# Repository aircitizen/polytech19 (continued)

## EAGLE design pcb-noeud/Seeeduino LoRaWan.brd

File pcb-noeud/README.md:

# PCB noeud

Ici se situent les fichiers EAGLE du PCB du noeud.
Il y a également la BOM et des images.

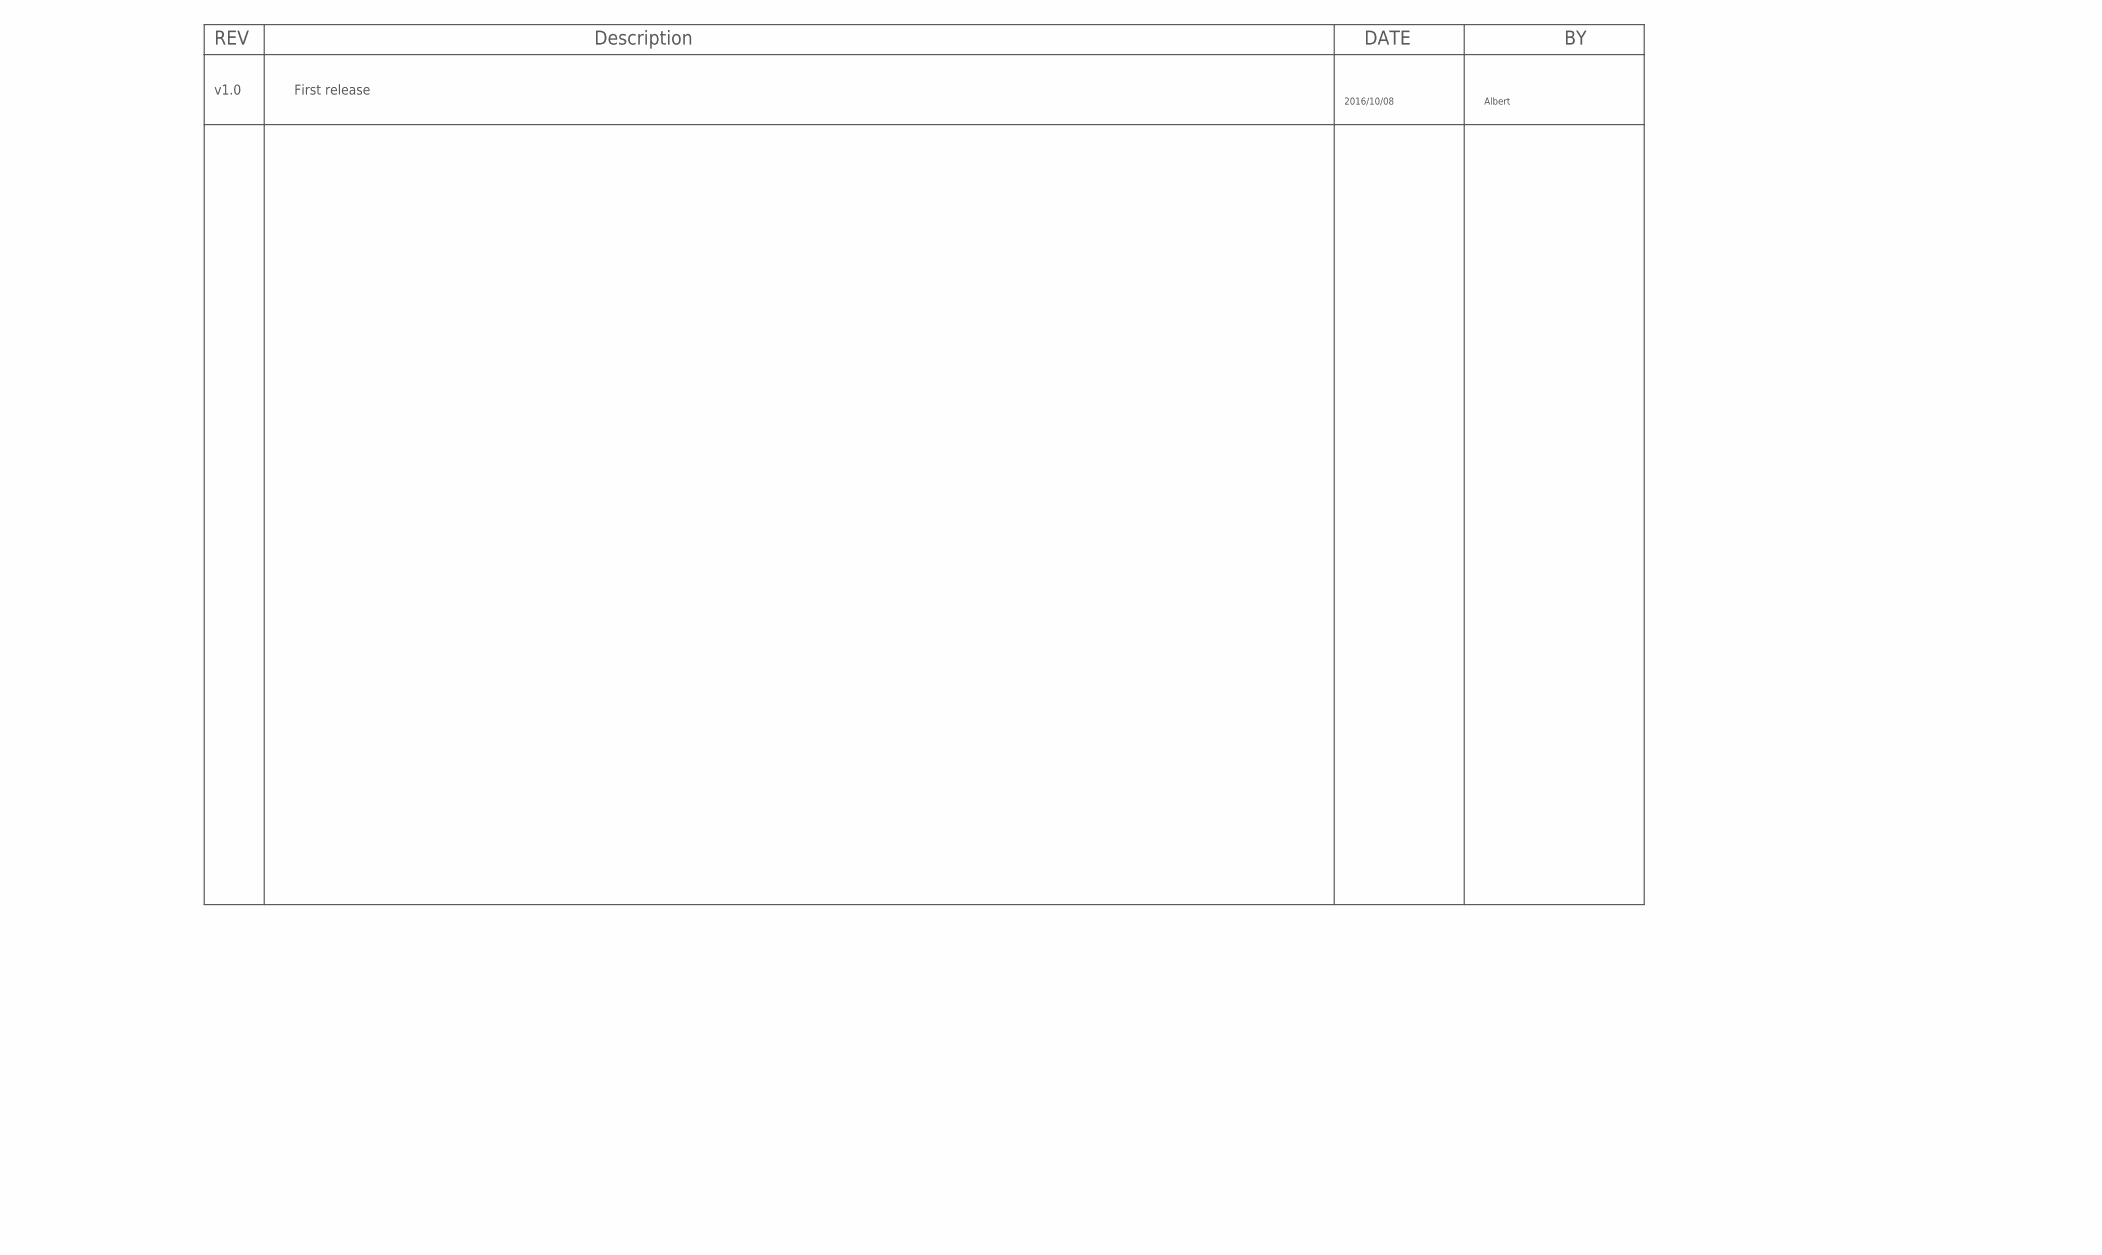
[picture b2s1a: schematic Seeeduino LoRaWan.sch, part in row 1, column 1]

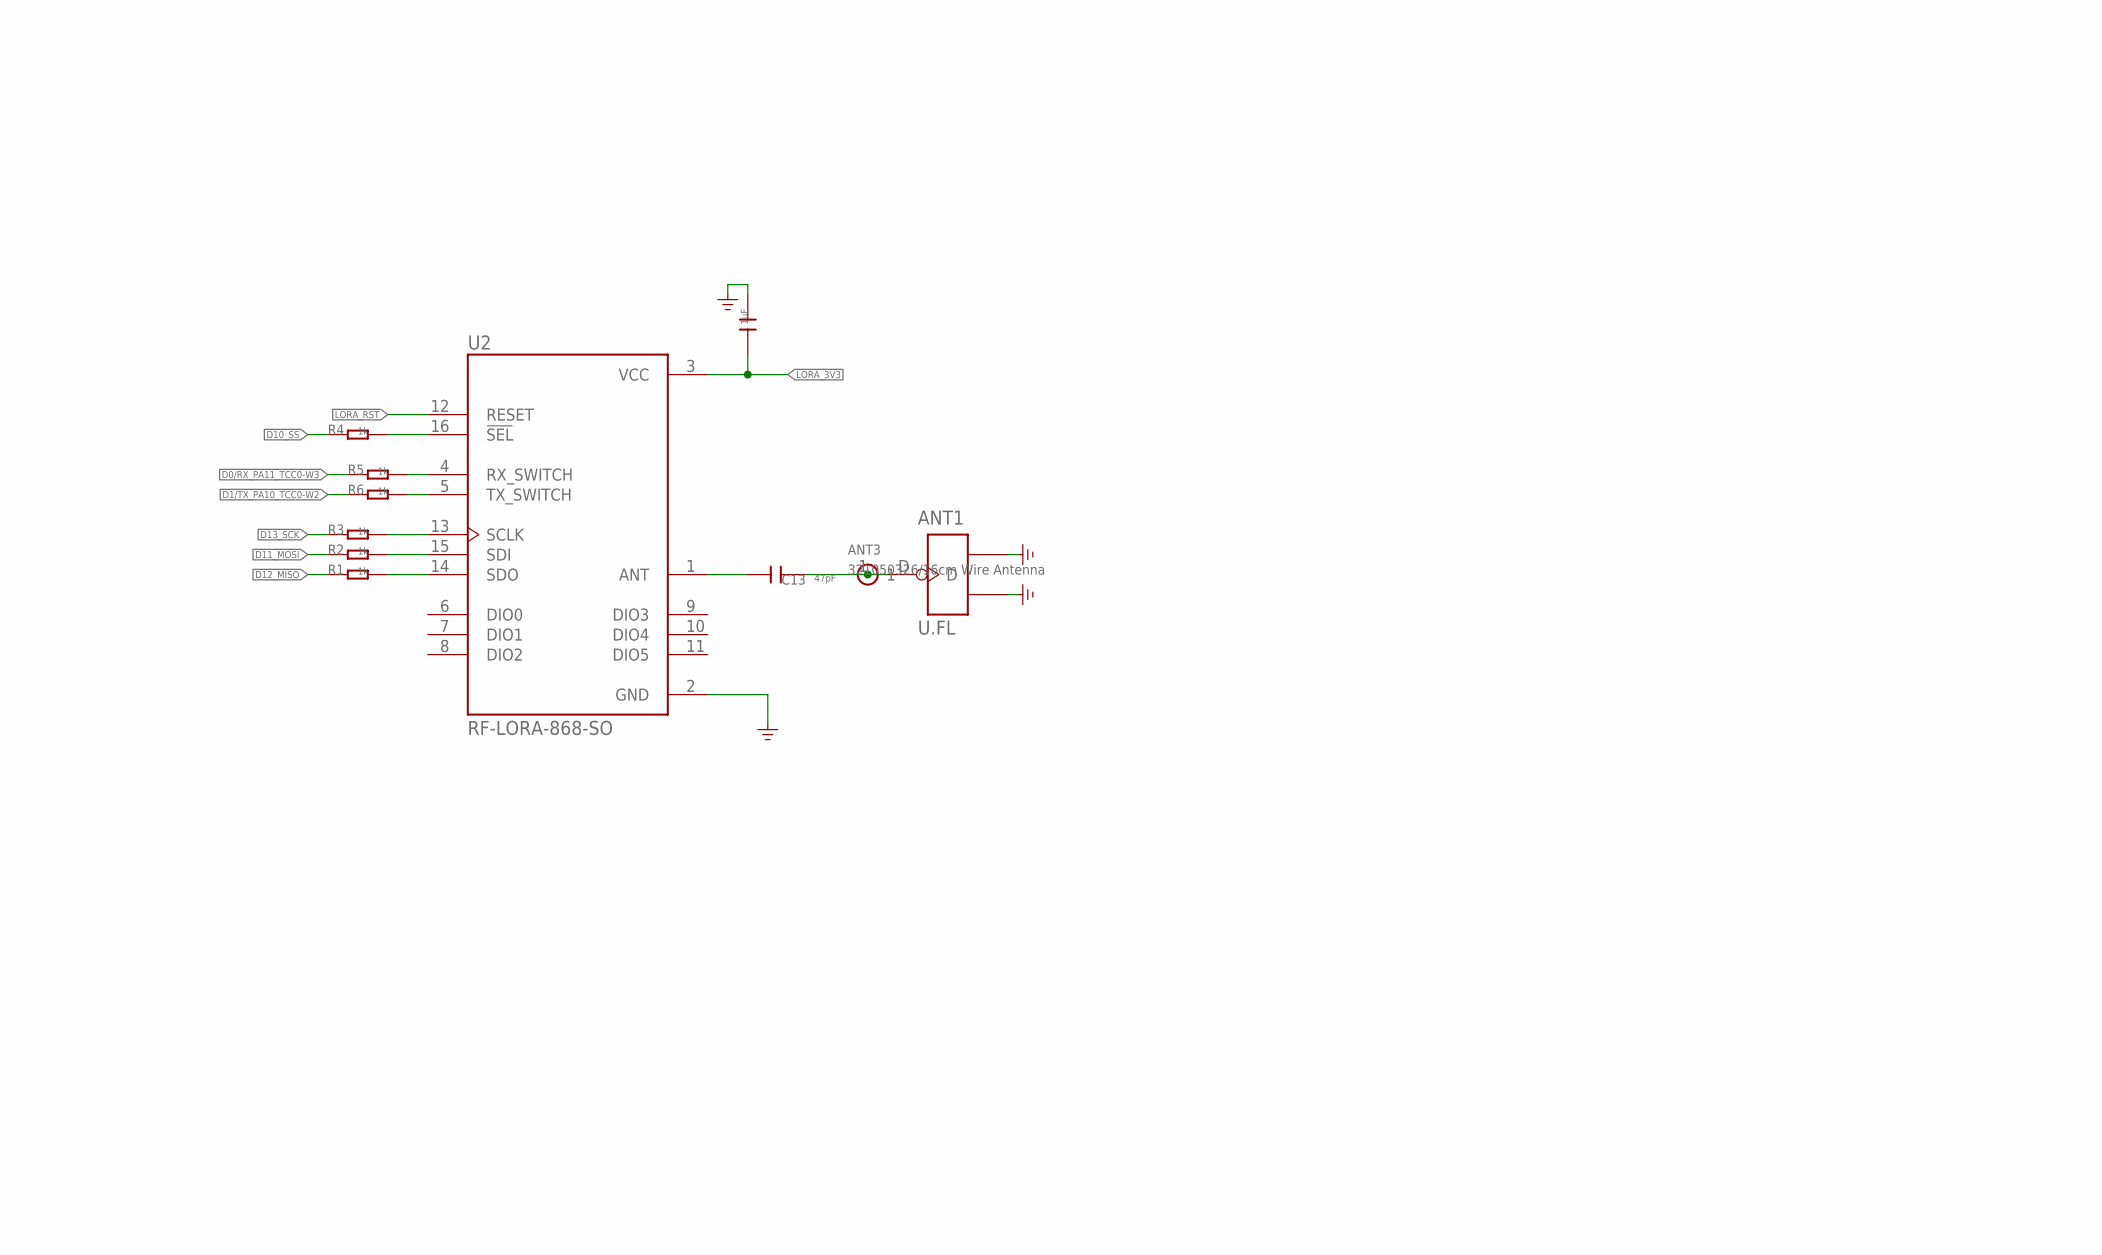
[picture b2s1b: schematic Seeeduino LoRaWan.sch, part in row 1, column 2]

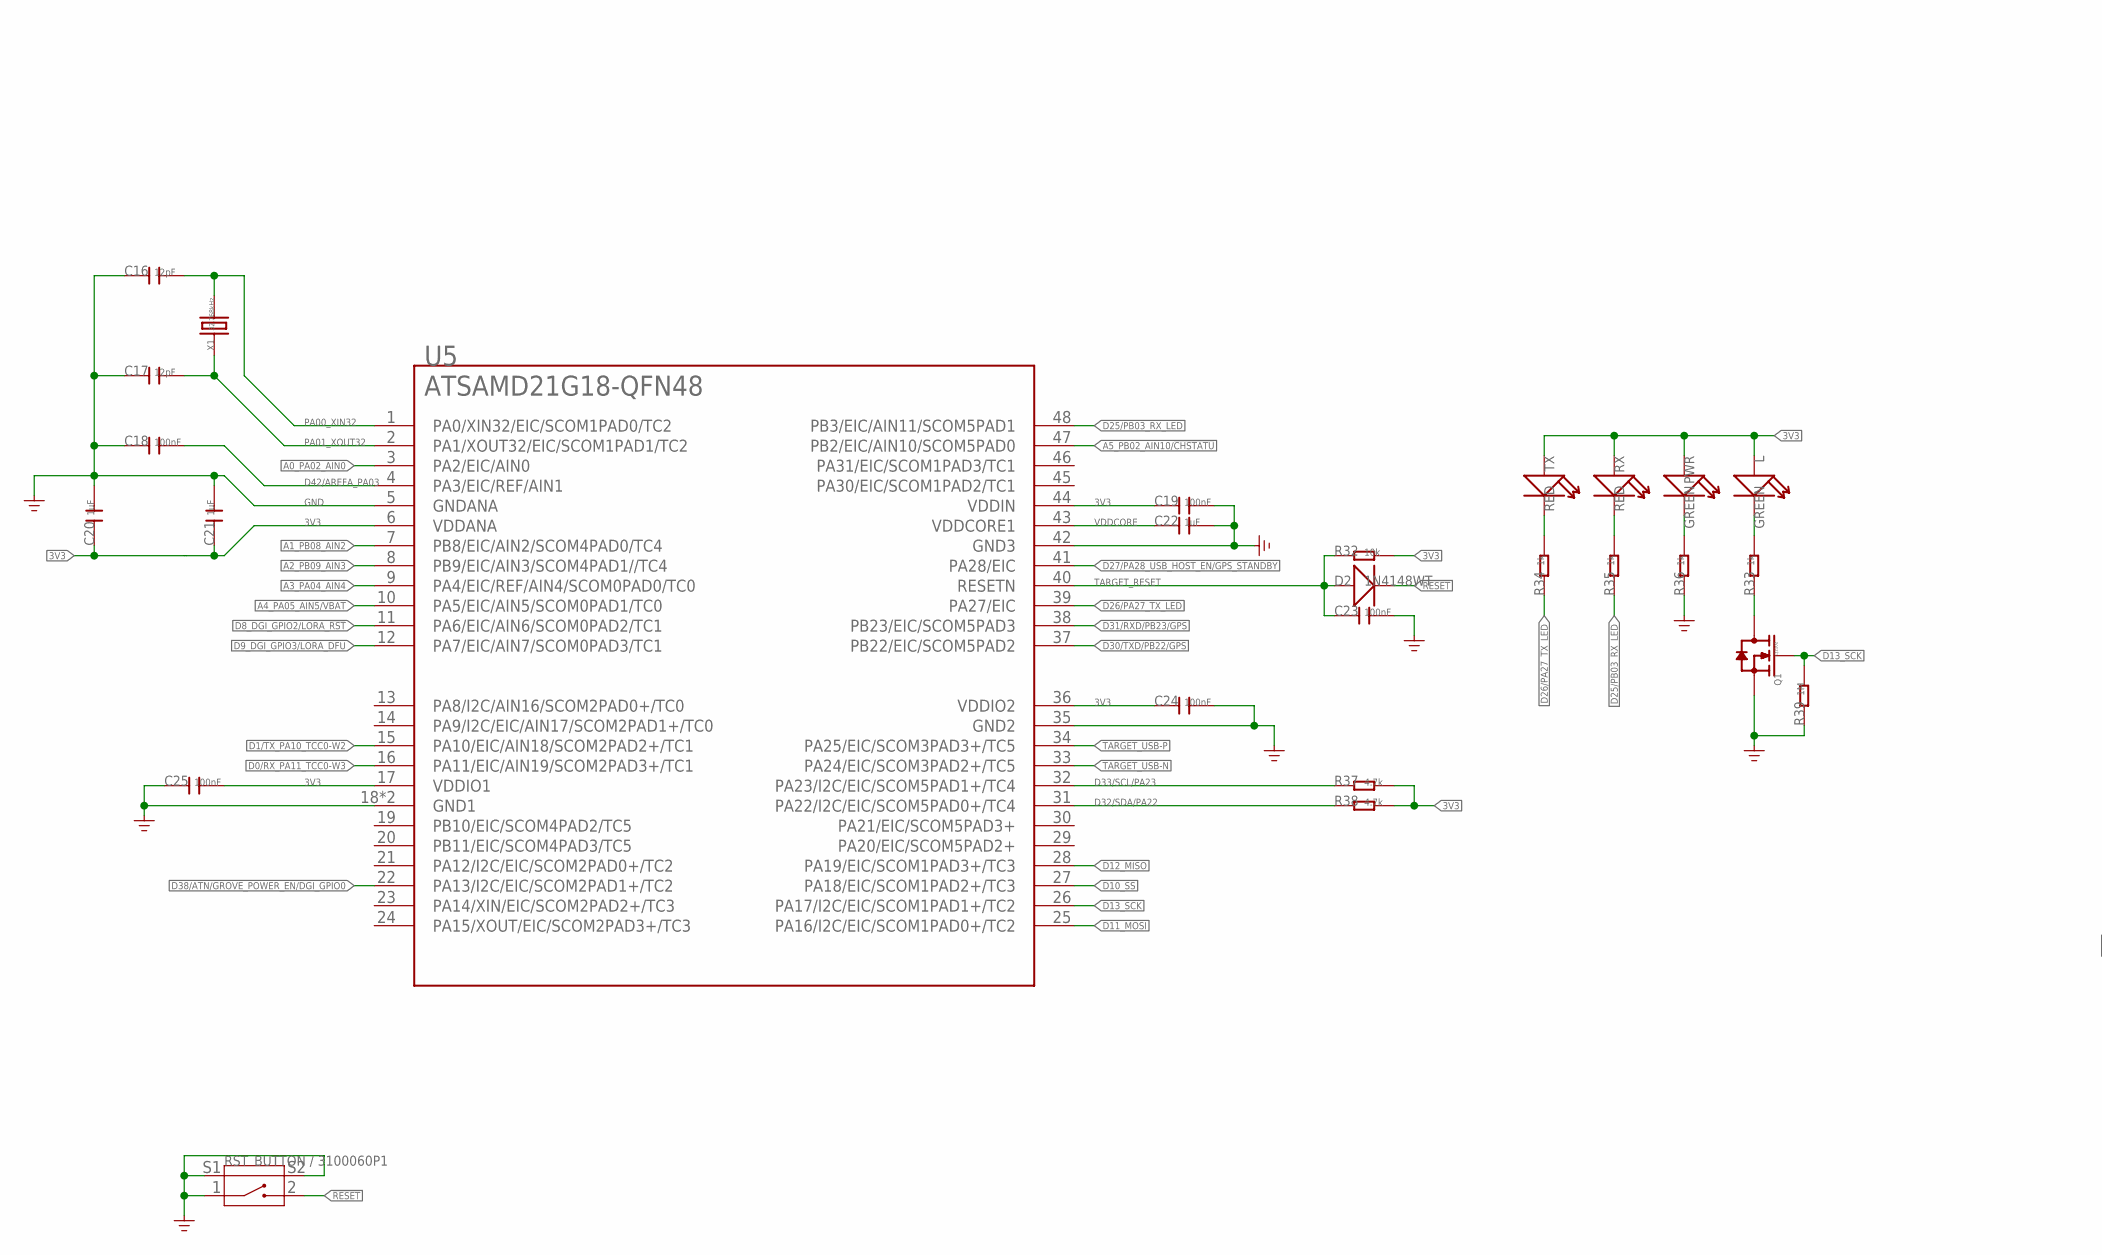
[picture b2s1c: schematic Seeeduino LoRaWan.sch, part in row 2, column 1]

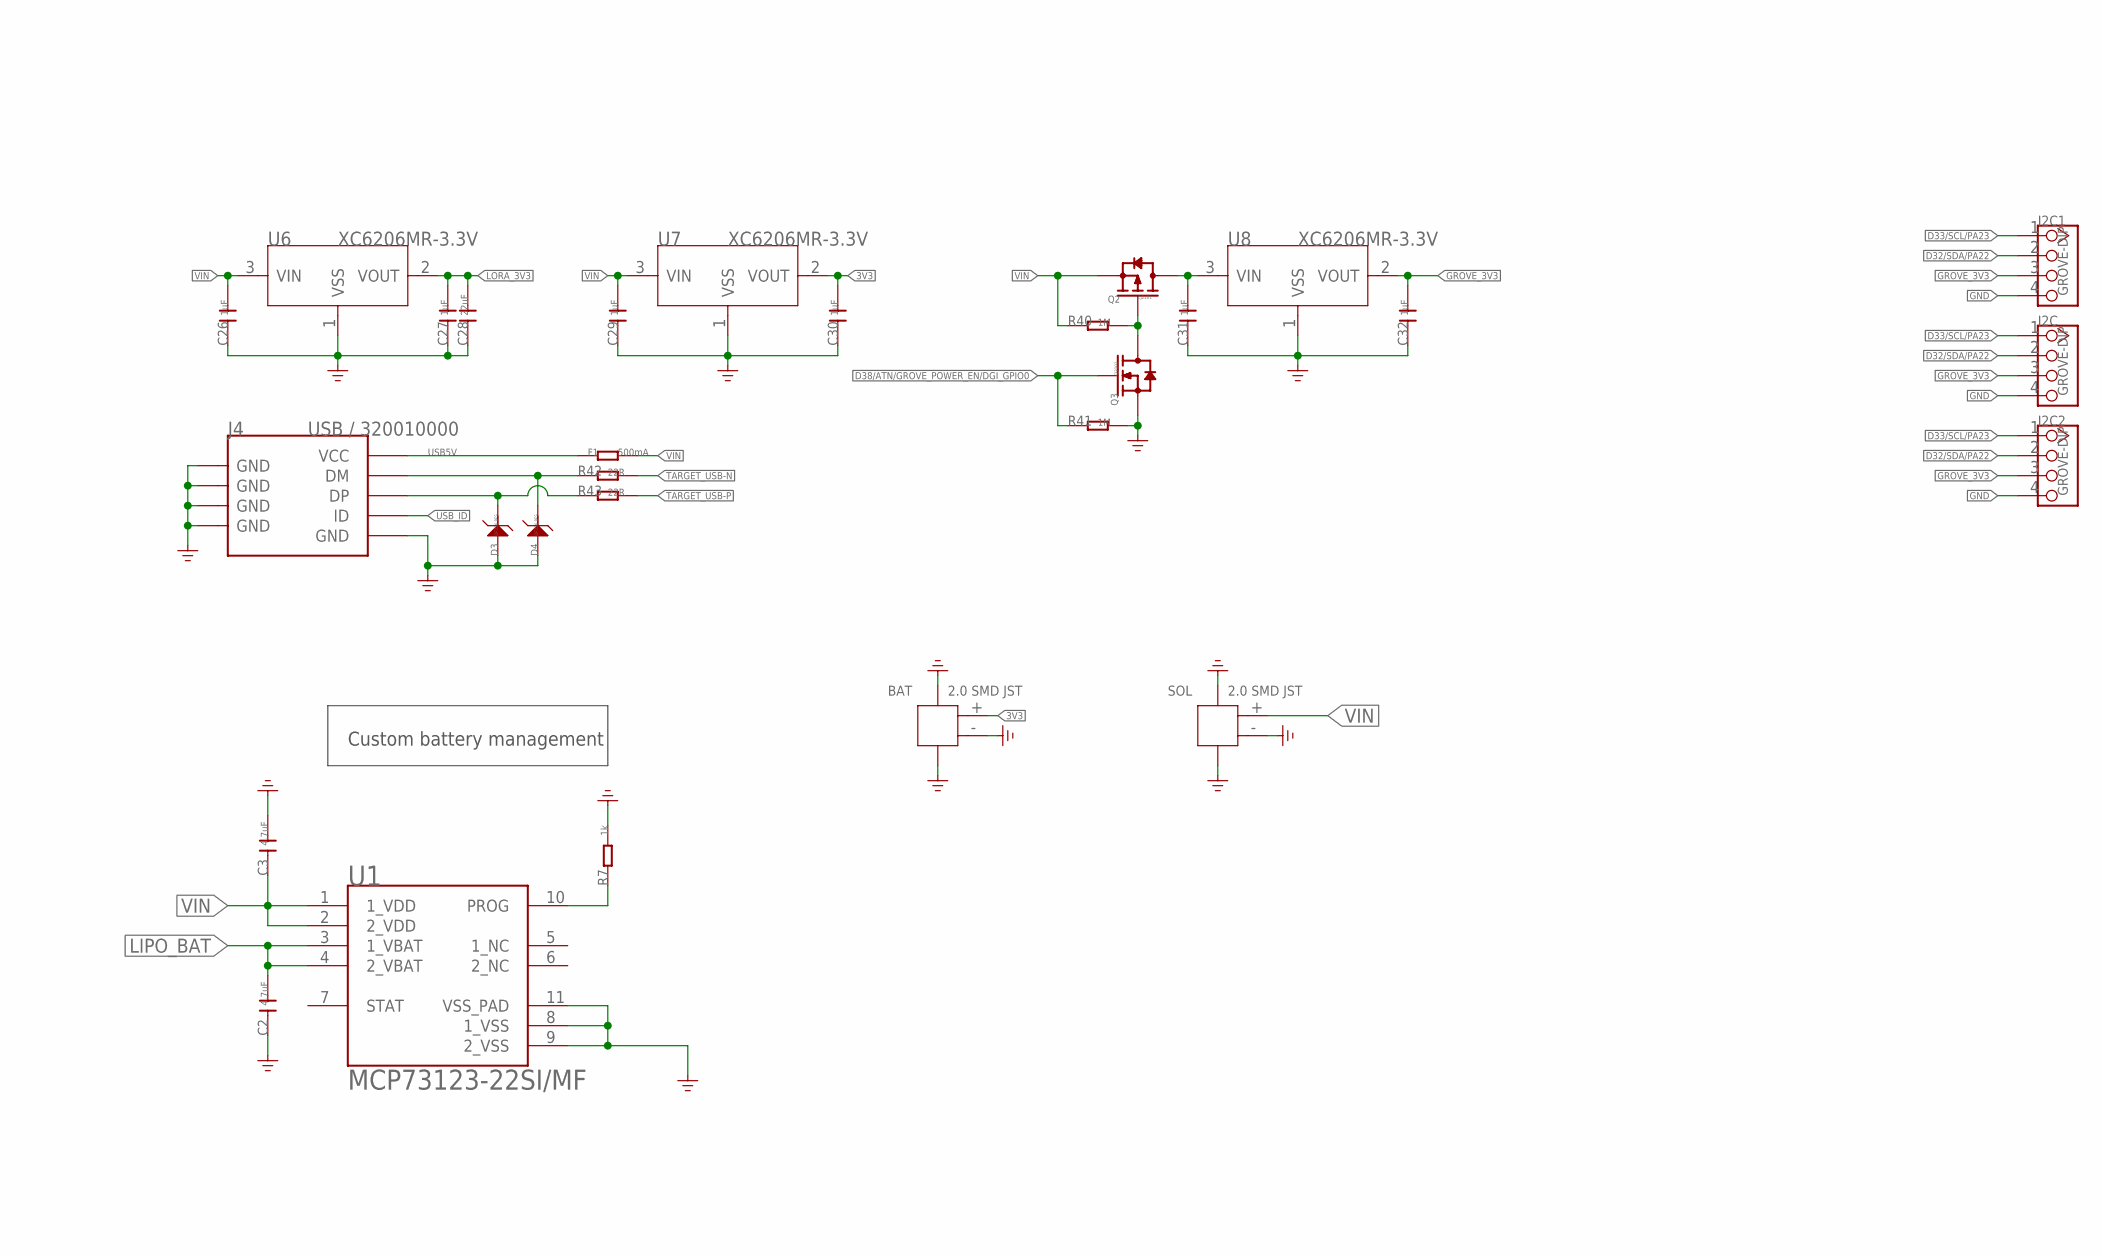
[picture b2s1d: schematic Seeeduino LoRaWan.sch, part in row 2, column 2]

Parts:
ANT1: U.FL; U-FL3P-SMD-2.6X2.6X1.0MM
ANT3: 321050326/16cm Wire Antenna; 1P-65/35MIL
BAT: 2.0 SMD JST; HW2-SMD-2.0-90D
C1, C20, C21, C22, C26, C27, C29, C30, C31, C32: 1uF; C0603
C2, C3: 4.7uF; C0603
C13: 47pF; C0603
C16, C17: 12pF; C0603
C18, C19, C23, C24, C25: 100nF; C0603
C28: 22uF; C0603
D2: 1N4148WT; SOD523
D3, D4: DF2S6.8FS; SOD-923
F1: 500mA; R0603
I2C, I2C1, I2C2: GROVE-DIP; 4P-2.0
J4: USB / 320010000; MICRO-USB
L: GREEN; LED-0603
PWR: GREEN; LED-0603
Q1, Q3: CJ2102; SOT-323
Q2: CJ2101; SOT323
R1, R2, R3, R4, R5, R6, R7, R33, R34, R35, R36: 1k; R0603
R32: 10k; R0603
R37, R38: 4.7k; R0603
R39, R40, R41: 1M; R0603
R42, R43: 22R; R0603
RST: BUTTON / 3100060P1; 4P-SMD-7.0X3.5X3.5H-90D
RX: RED; LED-0603
SOL: 2.0 SMD JST; HW2-SMD-2.0-90D
TX: RED; LED-0603
U1: MICROCHIP_MCP73123-22SI-MFMICROCHIP_MCP73123-22SI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; MICROCHIP_MCP73123-22SI-MF_0
U2: RF-LORA-868-SO; XCVR_RF-LORA-868-SO
U5: ATSAMD21G18-QFN48; QFN48-7X7
U6, U7, U8: XC6206MR-3.3V; SOT23
X1: 32.768kHz; X2-SMD-3.2X1.5X0.55MM

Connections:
3V3: BAT.+ (1), C19.1, C20.1, C21.1, C24.1, C25.2, C30.2, L.+, PWR.+, R32.2, R37.2, R38.2, RX.+, TX.+, U5.6 (VDDANA), U5.17 (VDDIO1), U5.36 (VDDIO2), U5.44 (VDDIN), U7.2 (VOUT)
!RESET: D2.-, RST.2
A0_PA02_AIN0: U5.3 (PA2/EIC/AIN0)
A1_PB08_AIN2: U5.7 (PB8/EIC/AIN2/SCOM4PAD0/TC4)
A2_PB09_AIN3: U5.8 (PB9/EIC/AIN3/SCOM4PAD1//TC4)
A3_PA04_AIN4: U5.9 (PA4/EIC/REF/AIN4/SCOM0PAD0/TC0)
A4_PA05_AIN5/VBAT: U5.10 (PA5/EIC/AIN5/SCOM0PAD1/TC0)
A5_PB02_AIN10/!CHSTATU: U5.47 (PB2/EIC/AIN10/SCOM5PAD0)
D0/RX_PA11_TCC0-W3: R5.1, U5.16 (PA11/EIC/AIN19/SCOM2PAD3+/TC1)
D1/TX_PA10_TCC0-W2: R6.1, U5.15 (PA10/EIC/AIN18/SCOM2PAD2+/TC1)
D8_DGI_GPIO2/LORA_!RST: U5.11 (PA6/EIC/AIN6/SCOM0PAD2/TC1)
D9_DGI_GPIO3/LORA_DFU: U5.12 (PA7/EIC/AIN7/SCOM0PAD3/TC1)
D10_SS: R4.1, U5.27 (PA18/EIC/SCOM1PAD2+/TC3)
D11_MOSI: R2.1, U5.25 (PA16/I2C/EIC/SCOM1PAD0+/TC2)
D12_MISO: R1.1, U5.28 (PA19/EIC/SCOM1PAD3+/TC3)
D13_SCK: Q1.1 (G), R3.1, R39.2, U5.26 (PA17/I2C/EIC/SCOM1PAD1+/TC2)
D25/PB03_RX_LED: R35.1, U5.48 (PB3/EIC/AIN11/SCOM5PAD1)
D26/PA27_TX_LED: R34.1, U5.39 (PA27/EIC)
D27/PA28_USB_HOST_EN/GPS_STANDBY: U5.41 (PA28/EIC)
D30/TXD/PB22/GPS: U5.37 (PB22/EIC/SCOM5PAD2)
D31/RXD/PB23/GPS: U5.38 (PB23/EIC/SCOM5PAD3)
D32/SDA/PA22: I2C.2, I2C1.2, I2C2.2, R38.1, U5.31 (PA22/I2C/EIC/SCOM5PAD0+/TC4)
D33/SCL/PA23: I2C.1, I2C1.1, I2C2.1, R37.1, U5.32 (PA23/I2C/EIC/SCOM5PAD1+/TC4)
D38/ATN/GROVE_POWER_EN/DGI_GPIO0: Q3.1 (G), R41.1, U5.22 (PA13/I2C/EIC/SCOM2PAD1+/TC2)
D42/AREFA_PA03: C18.2, U5.4 (PA3/EIC/REF/AIN1)
GND: ANT1.GND1, ANT1.GND2, BAT.3, BAT.4, BAT.- (2), C1.2, C2.1, C3.2, C16.1, C17.1, C18.1, C19.2, C20.2, C21.2, C22.2, C23.2, C24.2, C25.1, C26.1, C27.1, C28.1, C29.1, C30.1, C31.1, C32.1, D3.2 (1), D4.2 (1), I2C.4, I2C1.4, I2C2.4, J4.5 (GND), J4.S1 (GND), J4.S2 (GND), J4.S3 (GND), J4.S4 (GND), J4.S5 (GND), J4.S6 (GND), Q1.2 (S), Q3.2 (S), R7.2, R36.1, R39.1, R41.2, RST.1, RST.S1, RST.S2, SOL.3, SOL.4, SOL.- (2), U1.8 (1_VSS), U1.9 (2_VSS), U1.11 (VSS_PAD), U2.2 (GND), U5.5 (GNDANA), U5.18 (GND1), U5.35 (GND2), U5.42 (GND3), U5.PAD (GND1), U6.1 (VSS), U7.1 (VSS), U8.1 (VSS)
GROVE_3V3: C32.2, I2C.3, I2C1.3, I2C2.3, U8.2 (VOUT)
LIPO_BAT: C2.2, U1.3 (1_VBAT), U1.4 (2_VBAT)
LORA_3V3: C1.1, C27.2, C28.2, U2.3 (VCC), U6.2 (VOUT)
unnamed: Q1.3 (D), R33.1
unnamed: R34.2, TX.-
unnamed: C13.2, U2.1 (ANT)
unnamed: R35.2, RX.-
unnamed: L.-, R33.2
unnamed: R1.2, U2.14 (SDO)
unnamed: D3.1 (2), J4.3 (DP), R43.1
unnamed: D4.1 (2), J4.2 (DM), R42.1
unnamed: ANT1.D, ANT3.1, C13.1
unnamed: PWR.-, R36.2
unnamed: R2.2, U2.15 (SDI)
unnamed: R3.2, U2.13 (SCLK)
unnamed: R4.2, U2.16 (!SEL)
unnamed: R5.2, U2.4 (RX_SWITCH)
unnamed: R6.2, U2.5 (TX_SWITCH)
unnamed: R7.1, U1.10 (PROG)
unnamed: C31.2, Q2.3 (D), U8.3 (VIN)
unnamed: Q2.1 (G), Q3.3 (D), R40.2
PA00_XIN32: C16.2, U5.1 (PA0/XIN32/EIC/SCOM1PAD0/TC2), X1.2
PA01_XOUT32: C17.2, U5.2 (PA1/XOUT32/EIC/SCOM1PAD1/TC2), X1.1
TARGET_RESET: C23.1, D2.+, R32.1, U5.40 (RESETN)
TARGET_USB-N: R42.2, U5.33 (PA24/EIC/SCOM3PAD2+/TC5)
TARGET_USB-P: R43.2, U5.34 (PA25/EIC/SCOM3PAD3+/TC5)
USB5V: F1.1, J4.1 (VCC)
USB_ID: J4.4 (ID)
VDDCORE: C22.1, U5.43 (VDDCORE1)
VIN: C3.1, C26.2, C29.2, F1.2, Q2.2 (S), R40.1, SOL.+ (1), U1.1 (1_VDD), U1.2 (2_VDD), U6.3 (VIN), U7.3 (VIN)

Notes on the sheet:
v1.0
First release
2016/10/08
Albert
Custom battery management

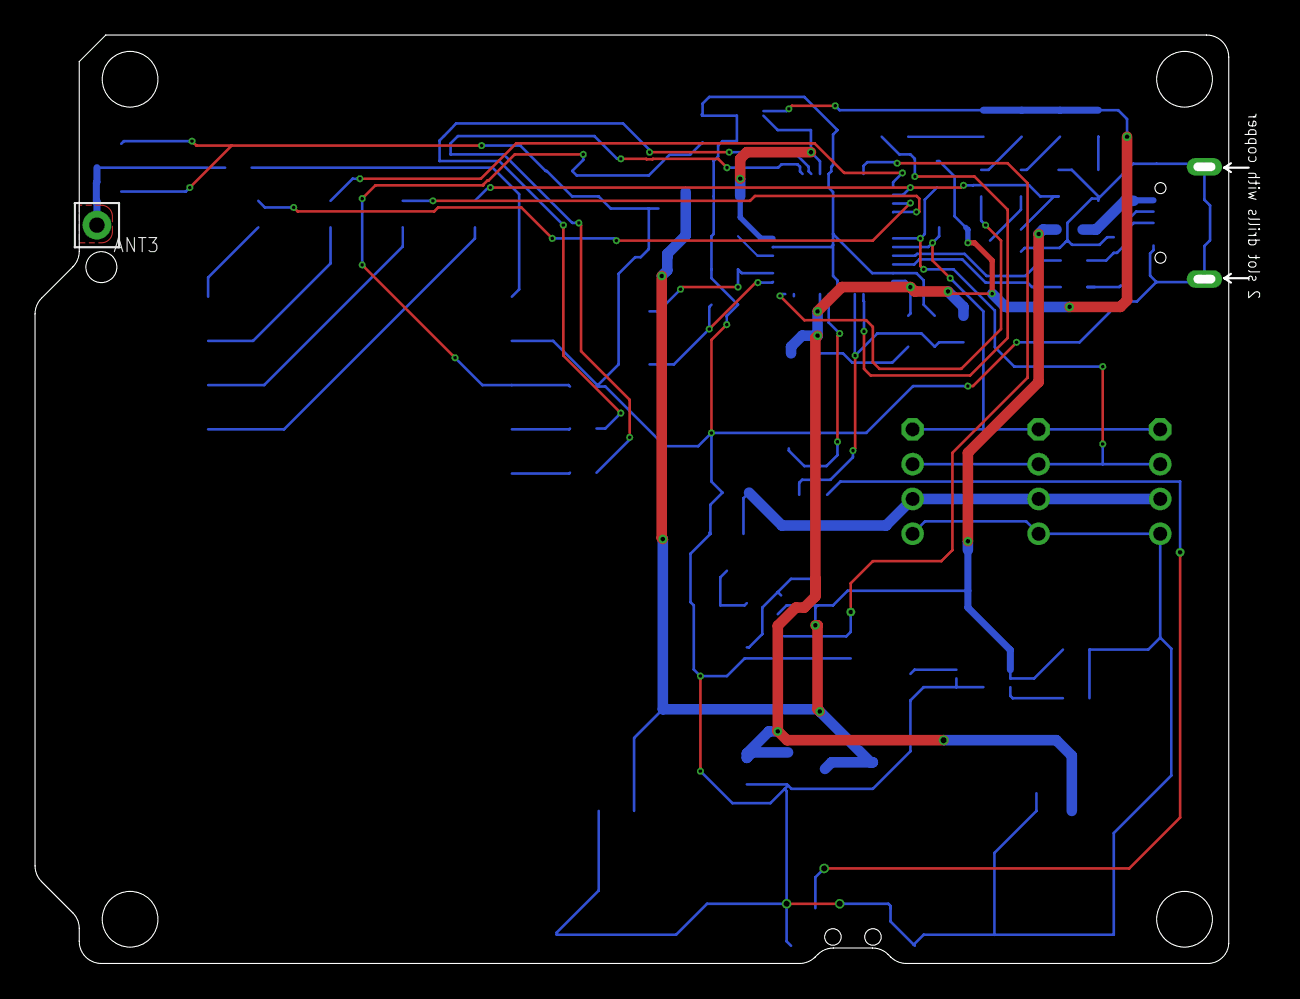
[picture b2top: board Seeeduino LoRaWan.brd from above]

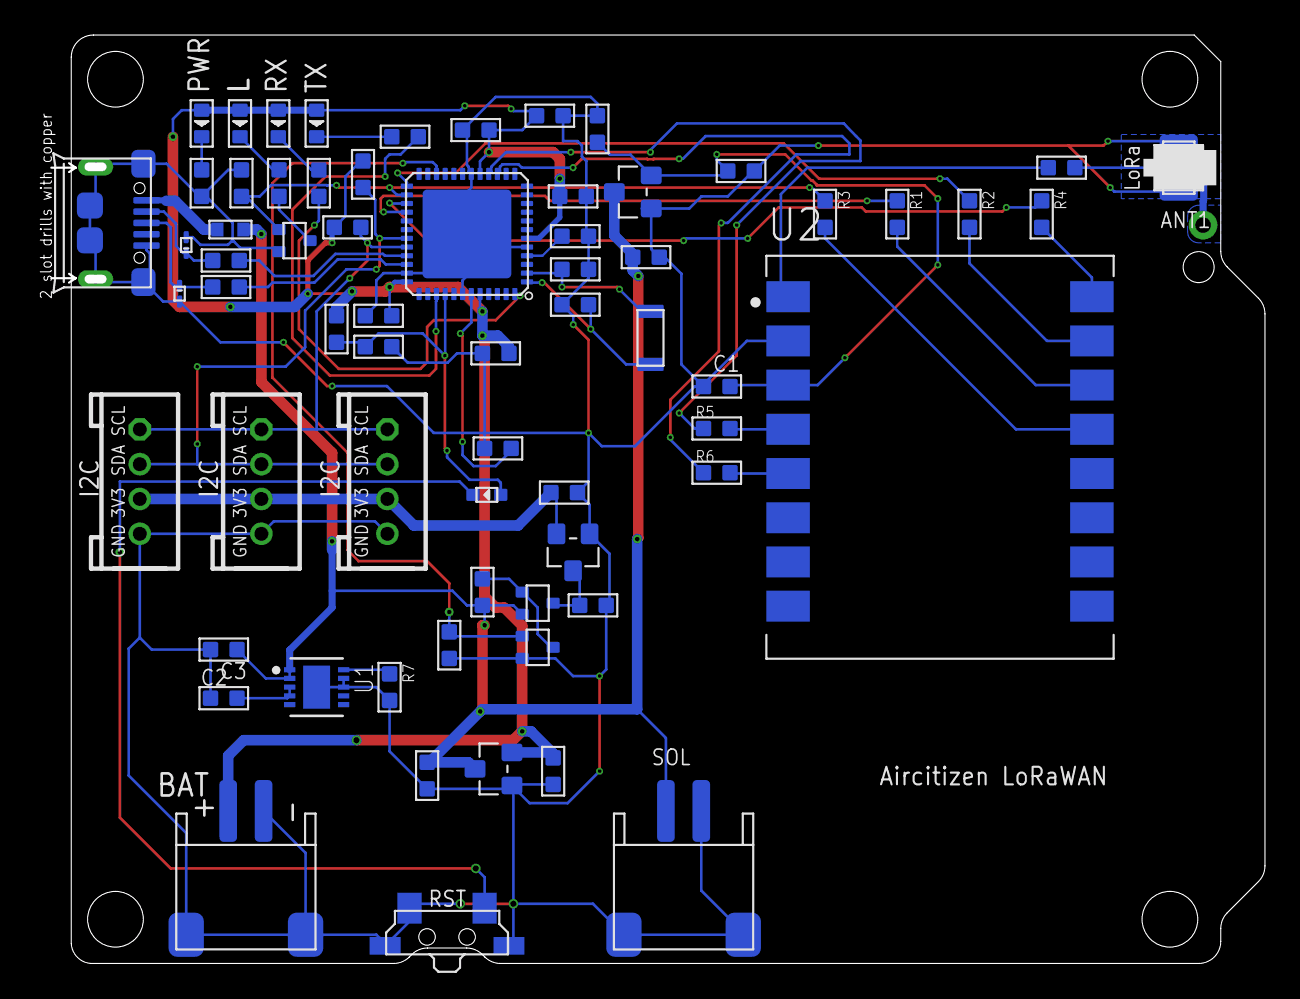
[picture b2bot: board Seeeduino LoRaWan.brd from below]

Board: 2 copper layers, 69.7 x 53.3 mm, 67 parts (66 on the bottom side), 44 nets.

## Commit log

2019-02-26 fichiers PCB noeud
2019-02-26 fichiers code arduino
2019-02-26 modif readme
2019-03-05 CodeNoeud1.1
2019-03-19 Final PCB
2019-04-02 Updated pictures
2019-04-02 Added Readme for both PCBs
2019-04-16 Added gateway files
2019-05-21 Updated gateway
2019-05-22 Update gateway and docs
2019-05-22 update name
2019-05-22 Update node code
2019-05-22 Reverted pins
